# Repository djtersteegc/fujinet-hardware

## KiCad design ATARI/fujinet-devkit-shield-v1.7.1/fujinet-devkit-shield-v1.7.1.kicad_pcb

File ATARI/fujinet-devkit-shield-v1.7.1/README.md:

# FujiNet DevKit Shield v1.7.1

This is an alternative hardware platform for Atari 8-bit [FujiNet](https://fujinet.online/) that allows you to build your own using all through-hole technology (THT) components and an Espressif ESP32-DevKitC-VE devkit board. You must use ESP32-WROVER based devkit boards, the cheaper ESP32-WROOM boards lack the PSRAM needed by the FujiNet firmware. 

This is an update to my original v1.0 version that matches Mozzwald's latest 1.7.1 schematic (hence the big version number bump) and improves the physical design a bit. It also include an option to cable with a real SIO cable.

[Schematic](https://djtersteegc.github.io/fujinet-hardware/Atari/schematic-fujinet-devkit-shield-v1.7.1.pdf)

# BOM

[Interactive BOM](https://djtersteegc.github.io/fujinet-hardware/Atari/ibom-fujinet-devkit-shield-v1.7.1.html)

For cabling you have a choice between direct wire with something like a 13 pin XH2.54 header, DB-15 female socket, or using either a real or [DIY SIO socket](../Atari-DIY-SIO-Socket-v1.0/README.md).

You can also use either an SMD Micro SD  connector and tantalum cap, or breakout board and THT tantalum. The current case is designed around the SMD option and it creates a much clear install, so I highly recommend that route, it's pretty easy to hand solder.

You will also need two 19p 2.54mm female header strips. I buy the the [40p versions](https://www.aliexpress.us/item/3256805857141565.html) and cut them down to size.

Make sure to buy the ESP32-DEVKITC-VE version of the devkit board. If you are in the US, [Amazon](https://www.amazon.com/gp/product/B087TNPQCV) is a great place to pick one of these up with Prime shipping.

The MicroSD sockets are readily available from [AliExpress](https://www.aliexpress.us/item/3256802643015074), [Amazon](https://www.amazon.com/Spring-Loaded-Transflash-Memory-Socket/dp/B0CDC5Q1HF), eBay and other places, sometimes called *Push Push TransFlash Socket*.

The "standard" FujiNet LED's colors are white for Wifi and orange for bus activity.

The case requires two M2.5x10mm countersunk screws. Longer scews up to 16mm will also work.

# Assembly

After installing the SMD components, proceed from shortest to tallest components.

See the [DIY SIO socket](../Atari-DIY-SIO-Socket-v1.0/README.md) repo for instructions on creating and assembling.

When it comes time to install the LED's, I place the board upside down in the case, and then use 1.2mm printed spacers to get a nice reveal of the LED domes just poking through the case top.

Here's all assembled without the ESP32 mounted on the female headers.

# Case

Pick the option to corresponds to your cabling choice.  If you have multiple color capability on your printer, you can use the [fujinet-devkit-shield-v1.7.1-embossed-text.stl](3D/STL/fujinet-devkit-shield-v1.7.1-embossed-text.stl) file to inlay colored text.  Make sure to print three copies of the buttons.  Assemble with M2.5x10mm countersunk screws.

# Flashing

Since the DevKit version has less flash than the SMD version, in FujiNet Flasher, you need to manually download the fujinet-ATARI-8mb-* (e.g. [fujinet-ATARI-8mb-v1.6.1.zip](https://github.com/FujiNetWIFI/fujinet-firmware/releases/download/v1.6.1/fujinet-ATARI-8mb-v1.6.1.zip)) firmware from the https://github.com/FujiNetWIFI/fujinet-firmware/releases page and then use the FujiNet Flasher to flash a Custom Firmware File.

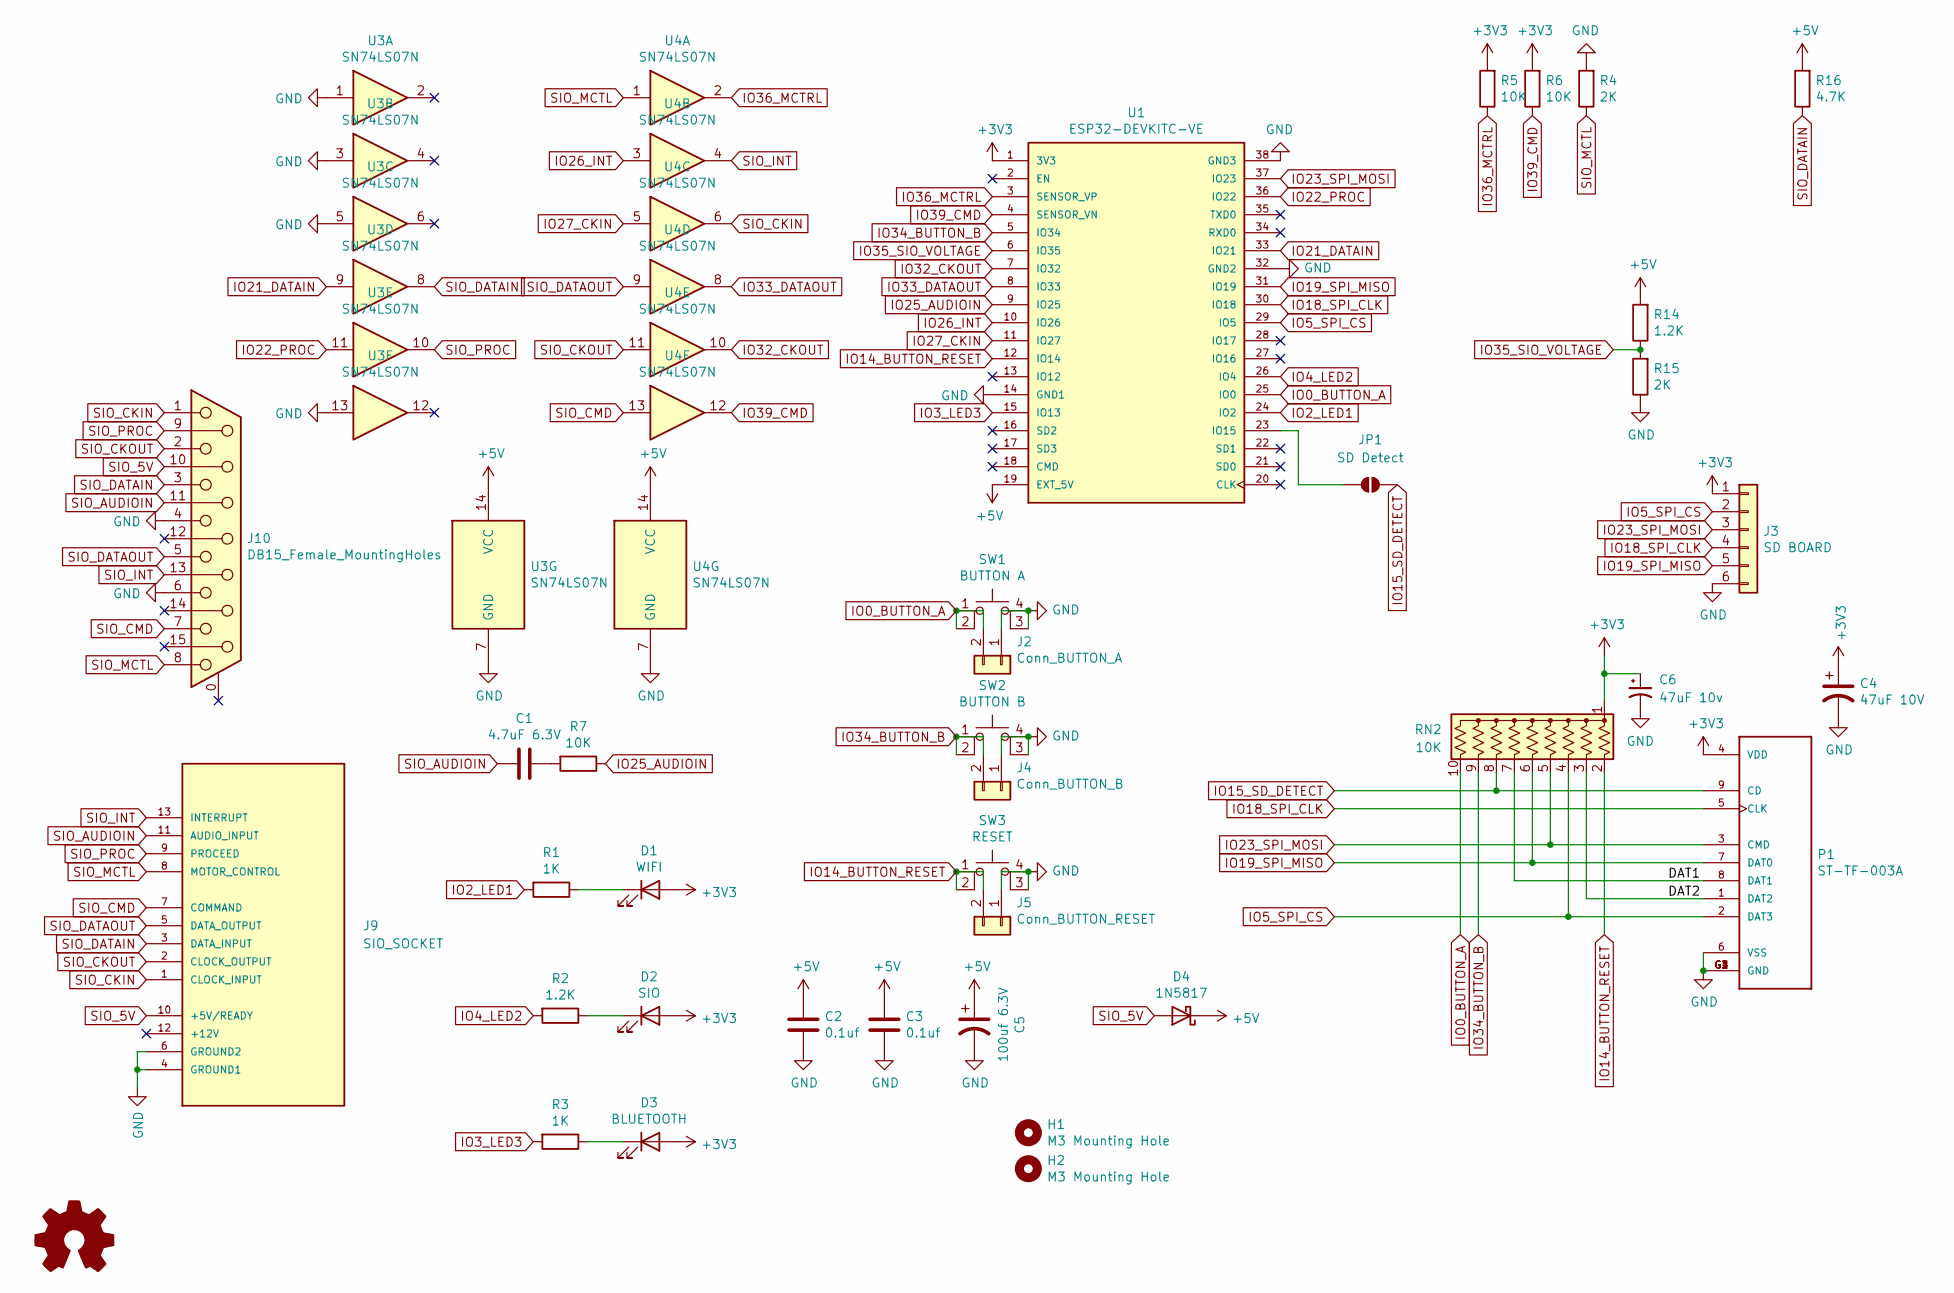
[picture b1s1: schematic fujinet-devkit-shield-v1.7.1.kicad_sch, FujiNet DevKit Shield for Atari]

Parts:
C1: 4.7uF 6.3V; C_Disc_D5.1mm_W3.2mm_P5.00mm
C2, C3: 0.1uf; C_Disc_D5.0mm_W2.5mm_P5.00mm
C4: 47uF 10V; CP_Radial_Tantal_D5.5mm_P5.00mm
C5: 100uf 6.3V; CP_Radial_D6.3mm_P2.50mm
C6: 47uF 10v; CP_EIA-3528-15_AVX-H_Pad1.50x2.35mm_HandSolder
D1: WIFI; LED_D5.0mm
D2: SIO; LED_D5.0mm
D3: BLUETOOTH; LED_D5.0mm
D4: 1N5817; D_DO-41_SOD81_P10.16mm_Horizontal
H1, H2: M3 Mounting Hole; MountingHole_2.7mm_M2.5
J2: Conn_BUTTON_A; PinHeader_1x02_P2.54mm_Vertical
J3: SD BOARD; PinHeader_1x06_P2.54mm_Vertical
J4: Conn_BUTTON_B; PinHeader_1x02_P2.54mm_Vertical
J5: Conn_BUTTON_RESET; PinHeader_1x02_P2.54mm_Vertical
J9: SIO_SOCKET; Atari SIO Socket Plus DIY Version
J10: DB15_Female_MountingHoles; DSUB-15_Female_Horizontal_P2.77x2.84mm_EdgePinOffset4.94mm_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
JP1: SD Detect; SolderJumper-2_P1.3mm_Open_RoundedPad1.0x1.5mm
P1: ST-TF-003A; SUNTECH_ST-TF-003A
R1, R3: 1K; R_Axial_DIN0207_L6.3mm_D2.5mm_P7.62mm_Horizontal
R2, R14: 1.2K; R_Axial_DIN0207_L6.3mm_D2.5mm_P7.62mm_Horizontal
R4, R15: 2K; R_Axial_DIN0207_L6.3mm_D2.5mm_P7.62mm_Horizontal
R5, R6, R7: 10K; R_Axial_DIN0207_L6.3mm_D2.5mm_P7.62mm_Horizontal
R16: 4.7K; R_Axial_DIN0207_L6.3mm_D2.5mm_P7.62mm_Horizontal
RN2: 10K; R_Array_SIP10
SW1: BUTTON A; SW_TH_Tactile_Omron_B3F-10xx
SW2: BUTTON B; SW_TH_Tactile_Omron_B3F-10xx
SW3: RESET; SW_TH_Tactile_Omron_B3F-10xx
U1: ESP32-DEVKITC-VE; MODULE_ESP32-DEVKITC-32U; PARTREV N/A
U3, U4: SN74LS07N; DIP-14_W7.62mm_Socket

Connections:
+3V3: C4.1, C6.1, D1.2 (A), D2.2 (A), D3.2 (A), J3.1, P1.4 (VDD), R5.2, R6.2, RN2.1 (common), U1.1 (3V3)
+5V: C2.1, C3.1, C5.1, D4.1 (K), R14.2, R16.2, U1.19 (EXT_5V), U3.14 (VCC), U4.14 (VCC)
/DAT1: P1.8 (DAT1), RN2.7 (R6)
/DAT2: P1.1 (DAT2), RN2.3 (R2)
GND: C2.2, C3.2, C4.2, C5.2, C6.2, J2.1, J3.6, J4.1, J5.1, J9.4 (GROUND1), J9.6 (GROUND2), J10.4, J10.6, P1.6 (VSS), P1.G1 (GND), P1.G2 (GND), P1.G3 (GND), P1.G4 (GND), R4.2, R15.1, SW1.3 (K), SW1.4 (A), SW2.3 (K), SW2.4 (A), SW3.3 (K), SW3.4 (A), U1.14 (GND1), U1.32 (GND2), U1.38 (GND3), U3.1, U3.3, U3.5, U3.7 (GND), U3.13, U4.7 (GND)
IO0_BUTTON_A: J2.2, RN2.10 (R9), SW1.1, SW1.2, U1.25 (IO0)
IO2_LED1: R1.2, U1.24 (IO2)
IO3_LED3: R3.2, U1.15 (IO13)
IO4_LED2: R2.2, U1.26 (IO4)
IO5_SPI_CS: J3.2, P1.2 (DAT3), RN2.4 (R3), U1.29 (IO5)
IO14_BUTTON_RESET: J5.2, RN2.2 (R1), SW3.1, SW3.2, U1.12 (IO14)
IO15_SD_DETECT: JP1.1 (A), P1.9 (CD), RN2.8 (R7)
IO18_SPI_CLK: J3.4, P1.5 (CLK), U1.30 (IO18)
IO19_SPI_MISO: J3.5, P1.7 (DAT0), RN2.6 (R5), U1.31 (IO19)
IO21_DATAIN: U1.33 (IO21), U3.9
IO22_PROC: U1.36 (IO22), U3.11
IO23_SPI_MOSI: J3.3, P1.3 (CMD), RN2.5 (R4), U1.37 (IO23)
IO25_AUDIOIN: R7.1, U1.9 (IO25)
IO26_INT: U1.10 (IO26), U4.3
IO27_CKIN: U1.11 (IO27), U4.5
IO32_CKOUT: U1.7 (IO32), U4.10
IO33_DATAOUT: U1.8 (IO33), U4.8
IO34_BUTTON_B: J4.2, RN2.9 (R8), SW2.1, SW2.2, U1.5 (IO34)
IO35_SIO_VOLTAGE: R14.1, R15.2, U1.6 (IO35)
IO36_MCTRL: R5.1, U1.3 (SENSOR_VP), U4.2
IO39_CMD: R6.1, U1.4 (SENSOR_VN), U4.12
unnamed: C1.2, R7.2
unnamed: D1.1 (K), R1.1
unnamed: D2.1 (K), R2.1
unnamed: D3.1 (K), R3.1
unnamed: JP1.2 (B), U1.23 (IO15)
SIO_5V: D4.2 (A), J9.10 (+5V/READY), J10.10
SIO_AUDIOIN: C1.1, J9.11 (AUDIO_INPUT), J10.11 (P111)
SIO_CKIN: J9.1 (CLOCK_INPUT), J10.1, U4.6
SIO_CKOUT: J9.2 (CLOCK_OUTPUT), J10.2, U4.11
SIO_CMD: J9.7 (COMMAND), J10.7, U4.13
SIO_DATAIN: J9.3 (DATA_INPUT), J10.3, R16.1, U3.8
SIO_DATAOUT: J9.5 (DATA_OUTPUT), J10.5, U4.9
SIO_INT: J9.13 (INTERRUPT), J10.13, U4.4
SIO_MCTL: J9.8 (MOTOR_CONTROL), J10.8, R4.1, U4.1
SIO_PROC: J9.9 (PROCEED), J10.9, U3.10

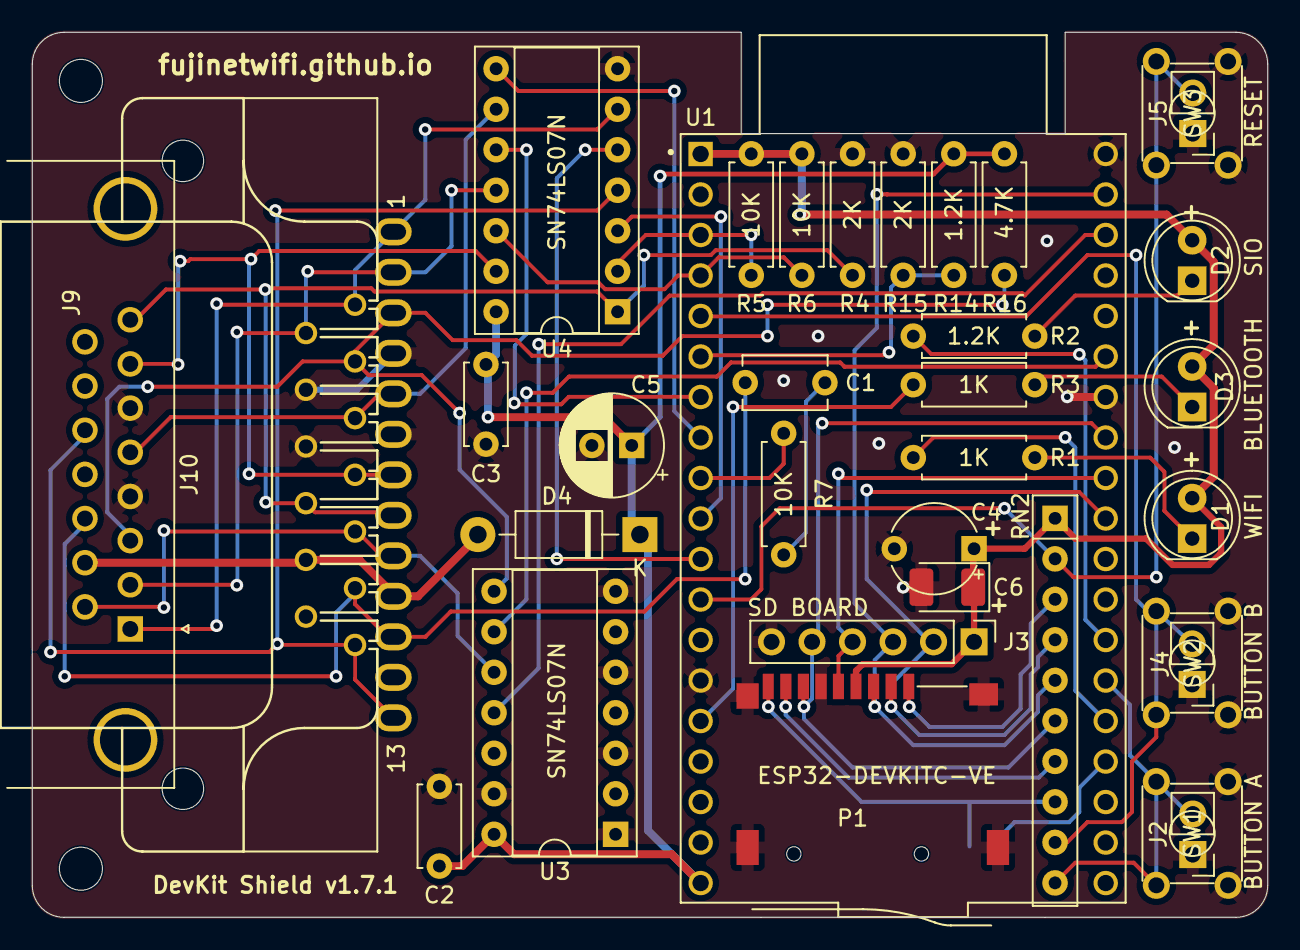
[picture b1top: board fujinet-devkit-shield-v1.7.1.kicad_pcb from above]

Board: 2 copper layers, 77.5 x 55.5 mm, 37 parts (1 on the bottom side), 41 nets.
